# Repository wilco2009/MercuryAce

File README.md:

# Mercury Ace - a Jupiter Ace clone

[English version](README.md)

[Versión en Español](LEEME.md)

An open hardware and open source project (this is a readonly copy of this git https://codeberg.org/wilco2009/Mercury_Ace)

With permision of Paul Andrews, current owner of the brand.

## FEATURES

- 3KB/19KB bytes of RAM selectable by a jumper
- Normal (black background) or inverse video (white background) selectable by a jumper
- composite video output
- Reset button
- 4+4 selectable ROMs
- Ace81 add-on (Beta)

## THE CIRCUIT

### THE MEMORY MAP

### WORK RAM

The work memory is where all program data is stored.

In a standard Jupiter Ace, we have only 1KB of working memory, although there are standard 16KB expansion modules that allow us to have 17KB of working memory.

The Mercury Ace has a jumper (J3) that allows us to select between 3KB of RAM and 19KB (1KB and 17KB of working memory, respectively):

- 3KB (1KB Work RAM + 1KB Char RAM + 1KB BG RAM)
- 19KB (17KB Work RAM + 1KB Char RAM + 1KB BG RAM)

The Z29 chip is responsible for generating the enable signal for the working RAM, which is located starting at address 0x3C00. There are three copies of the first K of this memory starting from 0x3000.

Z29 decodes A12-A14, and since it only activates when A15 = 0 (G2B), it is only active in the first 32K, providing an output for each region within these ranges:

- Y0: 0K-4K
- Y1: 4K-8K
- Y2: 8K-12K
- Y3: 12K-16K
- Y4: 16K-20K
- Y5: 20K-24K
- Y6: 24K-28K
- Y7: 28K-32K

The Z30C and Z30D gates are used to replicate the mirrors of the first KB of the working memory from the original circuit in the 12K-16K memory area.

A14 indicates if we are in the 8-16K area. When A14 = 0, they need to be repeated, so they are fixed to always access the same RAM.

- 3KB		/CE=!(!A14*A13*A12)

- 19KB	/CE=!((!A14*A13*A12) + A14)

### BG RAM

The screen memory or BGRAM resides in the Z5-6 chip. As we can see in the memory map, it occupies the address ranges 0x2400..0x27ff and 0x2000..0x23ff (mirror).

The logical equations that govern the chip are as follows:

Z29.Y2 = not (not A15 and not A14 and A13 and not A12)

R26.OUT = Z16.2Y2 + Z29.Y2

/WE1 = Z26.11

READING

 | A11  | R26.out | /WE1 | CE(CHR) | CE2(BG)  | OE |
 | -----| --------| -----| --------| ---------| ---|
 |  0   |   0     |  1   |    1    |   0      |  0 |
 |  0   |   1     |  1   |    0    |   0      |  0 |
 |  1   |   0     |  1   |    0    |   1      |  0 |
 |  1   |   1     |  1   |    0    |   0      |  0 |

WRITTING

 | A11  | R26.out | /WE1 | CE(CHR) | CE2(BG)  | OE |
 | -----| --------|------| --------| ---------| ---|
 |  0   |   0     |  0   |    1    |   0      |  1 |
 |  0   |   1     |  1   |    0    |   0      |  0 |
 |  1   |   0     |  0   |    0    |   1      |  1 |
 |  1   |   1     |  1   |    0    |   0      |  0 |

The screen memory is configured as a block of 32x24 characters, which represents 768 bytes, leaving 254 bytes unused at the end of this memory.

This block can be accessed for both reading and writing.

The address bus of this chip is accessed from the CPU through the Z15 and Z16 chips and from the video circuit through resistors R11 to R20.

Access from the CPU or the video circuit is managed by the /VHOLD signal.

In the table above, we can see the logic for chip activation.

The case A11:R26.out:/WE1 = 1:1:1 appears to incorrectly address the BGRAM and CHARRAM when the processor is accessing memory outside the video area, but thanks to the resistors located between the data bus and the BGRAM, priority is given to the WORKRAM and ROM.

### CHAR RAM

/WE1 = Z26.11

The character memory, or CHAR RAM, occupies the address ranges 0x2c00..0x2fff and 0x2800..0x2BFF (mirror), containing a set of 128 characters, which represents 128x8=1024 bytes.

The memory can be addressed both from the CPU and the video circuit, but the CPU can only access it in write mode.

The reason for this is that during reading, the address bus entering from Z17 and Z18 is connected to the data bus through a 1KB resistor array, and the output generated by the chip is also connected to the same data bus through another 1KB array. As a result, the addresses interfere with the output data, generating incorrect readings. 

One possible solution could be to make the resistance value of the first array (address) higher than that of the second array (data), giving priority to the latter. However, this would need to be tested to rule out any unforeseen consequences.

When the video circuit is accessing the CHARRAM, the address bus arrives via two paths:

- A4..A9 come from the data output of the BGRAM (D0..D6), which at that moment will contain the character being displayed.

- A0..A3 correspond to the scanline of the character currently being displayed and will come from the lower part of the line counter (CNT9..CNT11).

Additionally, bit 7 of the character code data coming from the BGRAM will be stored in latch Z27B. This bit will be used to invert the video in Z23D if the bit is 1.

Bits 0 to 6 of the character code from the BGRAM are loaded into the serializer (Z28) each time the three lower bits of the horizontal counter are at zero (CNT0..CNT2), and the pixels are output from the chip with each clock pulse, combining with bit 7 (inverse) at the Z23D gate.

### VIDEO RAM ACCESS PRIORITY

The circuit implements a priority system that allows priority access to the video RAM (BGRAM + CHARRAM) to the CPU or the video circuit.

The video memory is duplicated in the form of a mirror in two memory zones depending on the value of A10.

The priority of access to the VRAM is different depending on whether we access the main block (A10=1) or its copy (A10=0).

When we access the video memory from the CPU (A14:A13:A12 = 0:1:0) (output of R26) and /VHOLD=1 Z15 and Z16 allow the address to pass from the bus.

If the access occurs with /VHOLD=0, the circuit sets the 2Y2 output of Z16 to 1, isolating the signals from the address bus and allowing access from the video circuit.

Once set to 1, the signal is memorized and remains in that state until /VHOLD is 1 again, at which point it will again allow access from the CPU.

Z29.Y2 = (A14:A13:A12 = 0:1:0)

 | /VHOLD  |   Z29.Y2   | Z16.2Y2 |   1G   | next 2Y2  | ADDR_OUT  |
 | --------| -----------| --------| -------| ----------| ----------|
 |    1    |      0     |    -    |    0   |     x     |    ADDR   |
 |    1    |      1     |    -    |    1   |     x     |     x     |
 |    0    |      0     |    0    |    0   |     0     |    ADDR   |
 |    0    |      1     |    0    |    1   |     1     |     x     |
 |    0    |      -     |    1    |    1   |     1     |     x     |

For /VHOLD to be equal to 0 A10 must be equal to 1, which corresponds to the upper copy of the video RAM. /VHOLD also activates a mechanism by which it implements a wait state in the CPU through the Z80 /WAIT signal to avoid interference with the video circuit.

However, if A10=0 (lower copy) we will not activate the /VHOLD signal and therefore we will be able to consult the RAM thanks to the fact that resistors R11 to R20 will give priority to the CPU, so in this case we will interfere with the display and may show garbage on the screen during access.

/WAIT = /VHOLD + Z29.Y2

/VHOLD = !VIDEN + !A10 (/VHOLD active (=0) when VIDEN=0 and A10=0)

### VIDEO CIRCUIT

The video generation circuit is based on two 9-bit counters generated with the Z9, Z10 and Z11 chips:

The horizontal pixel counter corresponds to the CNT0..CNT8 signals.

The line counter corresponds to the CNT9..CNT17 signals.

From the counters the circuit generates two main signals; LINE and FIELD.

The LINE signal (Z22.12) is activated to indicate the end of each line when the horizontal counter is between 320 and 351:

LINE= !CNT5*!CNT7*CNT6*CNT8

The FIELD signal is activated to indicate the end of the display of a frame when the line counter is between 248 and 255:

    FIELD=CNT12*CNT13*CNT14*CNT15*CNT16

Additionally, the VIDEN signal indicates when the rectangle containing the characters is being represented, delimited between 0 and 255 for the horizontal counter and between 0 and 191 for the line counter.
 
    VIDEN = !(CNT16*CNT15)*!(CNT17+CNT8)
 
 |CNT17    | CNT16   | CNT15  | Line      | Comment           |
 | --------| --------| -------| ----------|-------------------|
 |   0     |   0     |   0    |  0-63     | Part of VIDEN     |
 |   0     |   0     |   1    |  64-127   | Part of VIDEN     |
 |   0     |   1     |   0    |  128-191  | Part of VIDEN     |
 |   0     |   1     |   1    |  192-255  | Not Part of VIDEN |
 |   1     |   x     |   x    |  256-311  | Not part of VIDEN |
 
 | CNT8 | Pixel  | Comment           |
 | -----| -------| ------------------|
 | 0    | 0-255  | Part of VIDEN     |
 | 1    |256-415 | Not part of VIDEN |

The display sequence starts with the pixel counter and the line counter being set to zero, a combination of bits from the line counter and the pixel counter determines the position of the first character to be displayed in the BGRAM.

1) To do this, the BGRAM is addressed with bits CNT3,4,5,6,7,12,13,14,15,16, which gives us the character code through pins D0..D7 of the chip.

2) The character code returned by the chip together with the three lower bits of the line counter (CNT9..11) are used to address chip Z7-8 and obtain the scanline with the definition of the character which is loaded into the serializer Z28.

3) Bit 7 of the character code (inverse bit) is stored in Z27B to be combined with the scanline bits through Z23D.

4) From that moment on, at each clock cycle, a bit of the serializer content is output through pin 13 of the same and is inverted or not in Z23D depending on the content of Z27B and sent to the display.

5) When the value of CNT0..2 is 0 again, a new character code is loaded and the first scanline of said character is started. This process is repeated, sending 32 characters to the monitor.

6) After this, the pixels corresponding to the right edge are sent.

7) From 320 to 351 (LINE) a SYNC signal (positive pulse) is generated.

8) Between 352 and 385 we generate the Backporch signal.

9) Between 386 and 415 the right edge is painted.

10) The counter is reset to 0.

11) The above sequence (2-10) is repeated for the next scanline up to a total of 8 (CNT9..11=111b) at which point we move on to addressing the next line in the BGRAM.

12) After displaying 24 lines (line counter=192) we move to the lower edge of the screen, generating the FIELD signal between the value 248 and 255 which causes a new SYNC signal. Additionally, an interrupt is generated in the Z80 /INT=0.

13) Finally, the upper edge of the screen is generated between 256 and 311.

14) When the line counter reaches the value 312 it is reset to 0 again and we begin displaying a new frame.

BACKPORCH = !CNT5*CNT2 from the last SYNC

### ACE81 ADDON (only valid until build025)

What is the ACE81 ADDON?
The ACE81 is a small module that plugs over the BGRAM and slightly modifies the display control hardware so that it is capable of managing a display like that of a ZX81.
The ZX81 makes extensive use of the processor to generate video, to the point that about two thirds of the processor's time is spent on this purpose.
The JA is a machine very similar to the ZX81 in many aspects, but with video generation hardware, which makes the 3.2MHz at which it operates fully available for our program.
The idea (and design) of the ACE81 came from Pedro Gimeno as an exercise in what a ZX81 would have been like if, like the JA, it had had dedicated hardware to generate video.
Obviously it would have been a much faster machine (or slower, depending on how we want to approach it).
The idea is to run a ZX81 ROM on a JA, with minimal modifications to the ROM to eliminate the video generation part.
Comparing the video memory of the ZX81 and the JA we realize that their layout is practically the same:

Similarities
- Both have 32x24 characters
- Both are black and white
- In both cases bit 7 of the character code is "inverse video"

Differences
- The character set of the JA is 128 elements, while in the ZX81 it is only 64 because bit 6=1 is used by the firmware to detect the end of line.
- In ZX81 each line is terminated in a HALT (cod=76h) (33x24=792 bytes) while in JA there is no line terminator (768 bytes)

Based on these premises the idea of ​​Ace81 is to make the video memory structure the same as that of the zx81 when we have activated the ZX81 mode (33 bytes per line), maintaining the standard structure (32 bytes per line) when the JA mode is selected.

Apart from the differences in the display, there is a small difference in the keyboard layout that requires modifying the circuitry of this to maintain the physical order of the keys.

Physically the layout of the keys of the ZX81 is identical to that of the JA, however unlike the JA, in the ZX81 the physical layout coincides with the logical one, which makes compatibility difficult when using a JA keyboard with the ZX81 ROM.
To overcome this problem, the keyboard wiring must be modified and some additional logic must be added, which we have decided to include in a GAL to facilitate the design.

As I mentioned before, the changes are limited to the two lower half-rows (half-row 0 and half-row 7).

| half-row| ZX81		      | Jupiter Ace	    |
|---------|-------------------|-----------------|
|    0    | SHIFT   Z   X C V | SHIFT SYMB Z X C|
|    7    | SPACE SYMB	N M B | SPACE  N   M B V|

But that small change and making both modes selectable, implies important modifications in the keyboard connection logic, since it completely changes the structure of the half-rows 0 and 7.

The equations that control both modes are the following:

```
/** Logic Equations **/

   ZX81 = ACE81_ENABLED;
   Jupiter = !ACE81_ENABLED;
   
   ROW_SS = !((Jupiter & !ROW1) # (ZX81 & !ROW8)); 
   ROW_V = !((Jupiter & !ROW8) # (ZX81 & !ROW1)); 
   
   KEYB2 = !(Jupiter & !KM & !ROW8 # ZX81 & !KZ & !ROW1 );
   KEYB3 = !(Jupiter & (!KN & !ROW8 # !KZ & !ROW1) # ZX81 & (!KM & !ROW8 # !KX & !ROW1)); 
   KEYB4 = !(Jupiter & (!KB & !ROW8 # !KX & !ROW1) # ZX81 & (!KN & !ROW8 # !KC &!ROW1));
   KEYB5 = !(Jupiter & !KC & !ROW1 # ZX81 & !KB & !ROW8);
```

### Hires plus 512KB memory ADDON (valid from Build026)

- Ace81 addon included 
- ROM page selected by software 
- High resolution 256x192 pixels 
- 32 pages in text-mode and 5 pages in high-resolution mode.
- 32 character sets in memory simultaneously.
- Shadow screen (CPU can access any of the video pages regardless of which one is currently being viewed).
- Extra 512KB of User RAM plus the internal 16KB

All the functionality of the Addon is managed via port E3, through a command system. 

Each command has its read equivalent, allowing us to check the status at any time. Below is a table with the available commands:

**Write mode**		

```
	ld a,cccddddd
	OUT ($e3),a
```
```  
	where 
        ccc = command;
        ddddd = param
```

| command |param         |description                             |
|---------|--------------|----------------------------------------|
| 000b	  |5 bit PAGE    |BG-RAM access page from CPU             |
| 001b	  |5 bit PAGE    |BG-RAM access page from video hardware  |
| 010b    |5 bit PAGE    |CHR-RAM access page from CPU            |
| 011b	  |5 bit PAGE    |CHR-RAM access page from video hardware |
| 100b	  |video mode    |00000b = Text mode, 00001b = Hires mode |
| 101b	  |4 bit PAGE    |USER RAM PAGE                           |
| 110b	  |0mppp         |(m=1 disable ace81)  ppp=ROM PAGE       |
| 111b	  |5bits subline |offset of hires page in lines           |
		
**Read mode**		

```
	ld a,ccc-----		
	in a,($e3)		
```
```  
	where 
        ccc = command;  returns result in register A"		
```

| command |result        |description                             |
|---------|--------------|----------------------------------------|
| 000b    |5 bit PAGE    |BG-RAM access page from CPU             |
| 001b	  |5 bit PAGE    |BG-RAM access page from video hardware  |
| 010b	  |5 bit PAGE    |CHR-RAM access page from CPU            |
| 011b	  |5 bit PAGE    |CHR-RAM access page from video hardware |
| 100b	  |video mode    |00000b = Text mode, 00001b = Hires mode |
| 101b	  |4 bit PAGE    |USER RAM PAGE                           |
| 110b	  |0mppp         |(m=1 disable ace81)  ppp=ROM PAGE       |
| 111b	  |5bits subline |offset of hires page in lines           |

### Operation of Video RAM and Character RAM Paging

The video and character RAM pages displayed are independently selectable from the video and character RAM pages accessed by the CPU.

For example, if we switch to page 1 with command 0, all CPU accesses will be redirected to page 1 of the BGRAM, but the video hardware will continue displaying page 0. The same applies to CHRRAM.

This configuration allows us to write in the background to a page that isn’t being displayed and then visualize it instantly by switching the active page for the hardware with command 1, avoiding glitches.

### Operation of Hires Mode

The Hires mode works by using 6 pages of text simultaneously (or 7, as we will see later), the BGRAM page selected for the hardware (henceforth referred to as VIDEO-BGPAGE) and the 5 subsequent pages.
The addressing space will continue to be 1024 bytes (2400h..27FFh), so it will be the programmer's responsibility to switch pages to access the 6KB of video memory.
Since each page has a size of 1KB, it will contain 32 lines (32*32=1024 bytes).

If we use only command 1, the hardware will start reading pixel line 0 from position 0 of the VIDEO-BGPAGE. However, using the page offset command (111b), we can specify a starting position offset (sub-line) within the VIDEO-BGPAGE.
This offset will affect only the display, while CPU access remains unaffected.
For example, if VIDEO-BGPAGE=0 and sub-line=10, the hardware will display the memory content starting at page 0, memory position 320 (32 bytes * 10 lines), and ending at page 7, position 319.

This command can be very useful for performing vertical scrolling via hardware.

Below, we can see a map of the video screen in high-resolution mode.

In this mode, the hardware displays characters with only one pixel of height, so the character definitions must match the binary representation of the code. The hires mode operation requires a prior configuration of character RAM. Before switching to hires mode, we must configure the character set as follows:

The first 4 scanlines of the active 128-character set must contain 4 copies of the character code in binary, and the last four scanlines should contain the character code XOR 127.

scanline/Addr |    0    |    8    |    16   |.........|  1016   |
--------------|---------|---------|---------|---------|---------|
 Addr+0       |00000000 |00000001 |00000010 |-------- |01111111 |
 Addr+1       |00000000 |00000001 |00000010 |-------- |01111111 |
 Addr+2       |00000000 |00000001 |00000010 |-------- |01111111 |
 Addr+3       |00000000 |00000001 |00000010 |-------- |01111111 |
 Addr+4       |01111111 |01111110 |01111101 |-------- |00000000 |
 Addr+5       |01111111 |01111110 |01111101 |-------- |00000000 |
 Addr+6       |01111111 |01111110 |01111101 |-------- |00000000 |
 Addr+7       |01111111 |01111110 |01111101 |-------- |00000000 |
 
### USER RAM PAGING

The 512KB of extra RAM for the user is set up in 32KB pages that occupy the second half of the Z80's addressing space.

The active page is selected using command 101b followed by the page number. Since we have 512KB of RAM, we have a total of 16 32KB pages.

### SWITCHING THE ACTIVE ROM BY SOFTWARE
Immediately after a reset, or when powering up the system, the active ROM will be the one selected by the ROM selection DIP switches. The ROM can be changed by software using command 110b followed by the ROM page. We have a total of 8 8KB ROM pages, so we need 3 bits for selection (bits 0 to 2 of register A).

### ACE81 MODE

Under normal conditions, ROMs 6 and 7 are reserved for ACE81 mode. This differs from the ACE81 addon, where ROMs 4, 5, 6, and 7 were reserved for this mode.

In addition to the previous change, the Hires Add-on includes an option to disable this mode so that ROMs 6 and 7 become normal ROMs. To disable ACE81 mode, use the ROM selection command. Setting bit 3 of register A to 1 during the ROM selection command call will disable ACE81 mode until the next reset or until the command is used again with bit 3 set to 0.

## ASSEMBLY

The Mercury Ace project is sponsored by [PCBWay](https://www.pcbway.com/)​. The high quality of their boards, the speed of manufacturing and shipping, and their high-tech process have greatly helped us achieve our goals.

Components that should be changed or should not be put in or changed during the assembly

- C4 – Do not place
- U2,R4,R32,R33,R34 – Do not place if SJ1 closes (video option)
- JP9 – Do not place if the Ace81 board is not in place
- SJ2-SJ9 – place if the Ace81 board is not in place
- R30 & R31 – Do not place if the Ace81 board is not in place
- D12.. D17 – install a 0R instead the diodes if the Ace81 board is not on
- JP17 - place always
- JP11 - place always 1-2,3-4,5-6,7-8,9-10
- JP12 - place always 1-2,3-4,5-6,7-8,9-10

We have the following options when building the board:

Installation of op-amp for video:

The SJ1 bridge is the one that will allow us to select whether to install the op-amp circuit or bypass it.

With the bridge open, the video will pass through the components of the op-amp and therefore we will need to install the following components:

-	U2
-	R4
-	R32
-	R33
-	R34

If you decide not to use the op-amp, you must close SJ1 with a drop of tin and not solder the aforementioned components.

Installing the Ace81 add-on module:

The Ace81 Add-On module is a circuit that is currently in Beta. This circuit modifies the Jupiter Ace's hardware to simulate a zx81, modifying the video generation circuit and keyboard order.

In the module we have a selector that will allow us to switch between Jupiter Ace mode and Ace81 mode.

If we want to have this add-on we must take in acount the follwing:

Do not install the following components: R30, R31, D12, D13, D14, D15, D16, D17, and Z40.
Bridge D12, D13, D14, D15, D16, and D17.

The JED file for the GAL(Z40) is available in the GAL folder.

Additionally, the Add-on board will have to be manufactured and connected on the pins located around the Z5-6 RAM (JP10x, JP15x, JP6 and JP8)

JP9 is an alternate selector on the main board for ACE81 mode, so JP9 and the Addon selector are mutually exclusive, so only one of them should be used, leaving the other one unset.

This mode requires a modified ROM for its proper functioning that is included inside the ROM folder.

The GAL must be welded without a socket as it does not fit inside the housing along with it.

If you do not use the Ace81 mode, you must take into account the following:

Install the following components: R30, R31, D12, D13, D14, D15, D16, D17, and Z40.

Close the JP10x, JP15x, JP6 and JP8 jumpers.

Close the SJ2 jumpers with a drop of tin. SJ9

## ROM

The clone allows to have 4 ROMs in Jupiter Ace mode and 4 ROMs in Ace81 mode, selectable from DIPSwitch S1. Pin 1 of S1 selects the mode (ON=ACE81 MODE, OFF=Jupiter ACE MODE).

The addon's mode selector will automatically switch between one block of 4 ROMs or the other, while S1 will allow you to manually select any of the 4 ROMs.

In the ROM folder we can find the following files:
- "ace.rom" - Original Jupiter Ace ROM
- "ace81.rom" - ZX81 ROM modified by Pedro Gimeno to work with the clone together with the Ace81 Add-on
- testrom.rom - diagnostics ROM made by Pedro Gimeno (https://codeberg.org/pgimeno/jupace-testrom)
- MercuryAce.bin - Contains all previous files in one unique file ready to be burned in an EEPROM.

| FILE      | MODE        | Z1.2 ADDR    | S1.1 | S1.2 | S1.3 |
| -----     | ------------| -------------| -----| -----| -----|
| ace.rom   | Jupiter Ace | 0000h..1fffh |  ON  |  ON  |  ON  |
| test.rom  | Jupiter Ace | 2000h..3fffh |  ON  |  ON  | OFF  |
| ace.rom   | Jupiter Ace | 4000h..5fffh |  ON  | OFF  |  ON  |
| test.rom  | Jupiter Ace | 6000h..7fffh |  ON  | OFF  | OFF  |
| ace81.rom | ZX81        | 8000h..9fffh | OFF  |  ON  |  ON  |
| test.rom  | ZX81        | a000h..bfffh | OFF  |  ON  | OFF  |
| ace81.rom | ZX81        | c000h..dfffh | OFF  | OFF  |  ON  |
| test.rom  | ZX81        | e000h..ffffh | OFF  | OFF  | OFF  |

## PARTLIST

### CLONE

 |Part	                               |Value   |Device     |Package    |Description	  |NO ACE81	     |ACE81	 |SJ1 CLOSED |SJ1 OPENED |
 | ------------------------------------| -------| ----------| ----------| ----------------| -------------| ------| ----------| ----------| 
 |K1..K41		                       |        |PUSH BUTTON|B3F-40     |OMRON	          |     Y        |  Y    |   Y       |   Y       |
 |R35                                  | 300R   |RESISTOR   |0204/7     |                 |	    Y		 |  Y    |   Y       |   Y       |
 |R26	                               | 330R   |RESISTOR   |0204/7     |                 |	    Y		 |  Y    |   Y       |   Y       |			
 |R28,R29                              | 680R   |RESISTOR   |0204/7     |                 |	    Y		 |  Y    |   Y       |   Y       |			
 |R32                                  | 200    |RESISTOR   |0204/7     |                 |	     		 |       |   N       |   Y       |			
 |R33                                  | 200    |RESISTOR   |0204/7     |                 |	     		 |       |   N       |   Y       |			
 |R34                                  | 75    |RESISTOR   |0204/7     |                 |	     		 |       |   N       |   Y       |			
 |R8,R10,R24,R25,R27,R39,R43           | 10K    |RESISTOR   |0204/7     |                 |	    Y		 |  Y    |   Y       |   Y       |			
 |R5                                   | 12K    |RESISTOR   |0204/7     |                 |	    Y		 |  Y    |   Y       |   Y       |			
 |R3                                   | 500R   |POT        |EU-B25P    | POTENTIOMETER   |	    Y		 |  Y    |   Y       |   Y       |			
 |R4                                   | 1K     |POT        |EU-B25P    | POTENTIOMETER   |	    Y		 |  Y    |   Y       |   Y       |			
 |R44                                  | 1K     |POT        |EU-B25P    | POTENTIOMETER   |	    Y		 |  Y    |   Y       |   Y       |			
 |R1,R6,R11..R23,R100..R107,R200..R207 | 1K     |RESISTOR   |0204/7     |                 |	     		 |       |   N       |   Y       |			
 |R42                                  | 1K     |RESISTOR   |0204/7     |                 |	     		 |       |   N       |   Y       |			
 |R45,R46,R47                          | 470R   |RESISTOR   |0204/7     |                 |	     		 |       |   N       |   Y       |			
 |R9                                   | 22K    |RESISTOR   |0204/7     |                 |	    Y		 |  Y    |   Y       |   Y       |			
 |R7                                   | 33K    |RESISTOR   |0204/7     |                 |	    Y		 |  Y    |   Y       |   Y       |			
 |R2                                   | 47K    |RESISTOR   |0204/7     |                 |	    Y		 |  Y    |   Y       |   Y       |			
 |R30,R31                              | 4K7    |RESISTOR   |0204/7     |                 |	    N		 |  Y    |   Y       |   Y       |			
 |R36..R38,R40,R41                     | 4K7    |RESISTOR   |0204/7     |                 |	    Y		 |  Y    |   Y       |   Y       |			
 |R45..R47                             | 470R   |RESISTOR   |0204/7     |                 |	    Y		 |  Y    |   Y       |   Y       |			
 |RN1 (alt to R36,R37,R38,R40,R41)     | 4K7    |RNET       |RN-6       | RESISTOR NET    |	    Y		 |  Y    |   Y       |   Y       |			
 |C4 (DO NOT INSTALL)                  |        |CAPACITOR  |025X50     | CERAMIC  CAP.   |	    N		 |  N    |   N       |   N       |			
 |C10,C13..C21                         | 100nF  |CAPACITOR  |025X50     | CERAMIC  CAP.   |	    Y		 |  Y    |   Y       |   Y       |			
 |C2                                   | 100pF  |CAPACITOR  |025X50     | CERAMIC  CAP.   |	    Y		 |  Y    |   Y       |   Y       |			
 |C9                                   | 100uF  |CAPACITOR  |RADIAL     | POL. CAPACITOR  |	    Y		 |  Y    |   Y       |   Y       |			
 |C7,C11,C12                           | 1uF    |CAPACITOR  |RADIAL     | POL. CAPACITOR  |	    Y		 |  Y    |   Y       |   Y       |			
 |C8                                   | 2.2nF  |CAPACITOR  |025X50     | CERAMIC  CAP.   |	    Y		 |  Y    |   Y       |   Y       |			
 |C3                                   | 2.2uF  |CAPACITOR  |025X50     | CERAMIC  CAP.   |	    Y		 |  Y    |   Y       |   Y       |			
 |C1                                   | 30pF   |CAPACITOR  |025X50     | CERAMIC  CAP.   |	    Y		 |  Y    |   Y       |   Y       |			
 |C22                                  | 470pF  |CAPACITOR  |025X50     | CERAMIC  CAP.   |	    Y		 |  Y    |   Y       |   Y       |			
 |C6                                   | 47nF   |CAPACITOR  |025X50     | CERAMIC  CAP.   |	    Y		 |  Y    |   Y       |   Y       |			
 |C5                                   | 47pF   |CAPACITOR  |025X50     | CERAMIC  CAP.   |	    Y		 |  Y    |   Y       |   Y       |			
 |C23                                  | 10pF   |CAPACITOR  |025X50     | CERAMIC  CAP.   |	    Y		 |  Y    |   Y       |   Y       |			
 |D1..D11                              | 1N4148 |DIODE      |DO35-7     | SIGNAL DIODE    |	    Y		 |  Y    |   Y       |   Y       |			
 |D12..D17                             | 1N4148 |DIODE      |DO35-7     | SIGNAL DIODE    | REP.WITH 0R  |  Y    |           |           |			
 |U1                                   | 7805   |REGULATOR  |TO220      | 5V REGULATOR    |      Y       |  Y    |   Y       |   Y       |			
 |Q1                                   | 2N3904 |TRANSISTOR |TO92       | NPN             |      Y       |  Y    |   Y       |   Y       |			
 |X1                                   | 6.5MHZ |CRISTAL    |HC49U      |                 |      Y       |  Y    |   Y       |   Y       |			
 |Z0                                   | Z80A   |CPU        |DIL40      |                 |      Y       |  Y    |   Y       |   Y       |			
 |Z1-2                                 | 27C512 |EEPROM     |DIL28W     | 64KB x 8 BITS   |      Y       |  Y    |   Y       |   Y       |			
 |Z1,Z27                               | 74LS74 |74XX       |DIL14      | DUAL D-FLIP FLOP|      Y       |  Y    |   Y       |   Y       |			
 |Z3-4,Z5-6,Z7-8                       | 62256  |SRAM       |DIL28W     | 32KB x 8 BITS   |      Y       |  Y    |   Y       |   Y       |			
 |Z9,Z10,Z11                           | 74LS393|74XX       |DIL14      | DUAL BIN.COUNTER|      Y       |  Y    |   Y       |   Y       |			
 |Z14..Z18                             | 74LS367|74XX       |DIL16      | 3-STATE BUFFER  |      Y       |  Y    |   Y       |   Y       |			
 |Z19,Z30,Z41                          | 74LS00 |74XX       |DIL14      | 4xNAND GATES    |      Y       |  Y    |   Y       |   Y       |			
 |Z20                                  | 74LS08 |74XX       |DIL14      | 4xAND GATES     |      Y       |  Y    |   Y       |   Y       |			
 |Z21,Z22,Z31                          | 74LS11 |74XX       |DIL14      | 3xAND GATES     |      Y       |  Y    |   Y       |   Y       |			
 |Z23                                  | 74LS86 |74XX       |DIL14      | 4xXOR GATES     |      Y       |  Y    |   Y       |   Y       |			
 |Z24,Z25                              | 74LS02 |74XX       |DIL14      | 4xNOR GATES     |      Y       |  Y    |   Y       |   Y       |			
 |Z26                                  | 74LS32 |74XX       |DIL14      | 4xOR GATES      |      Y       |  Y    |   Y       |   Y       |			
 |Z29                                  | 74LS138|74XX       |DIL16      | DECODER         |      Y       |  Y    |   Y       |   Y       |			
 |Z28                                  | 74LS166|74XX       |DIL16      | 8BIT SHIFT REG. |      Y       |  Y    |   Y       |   Y       |			
 |Z40                                  | GAL16V8|GAL        |DIL20      | GAL16V8         |      N       |  Y    |           |           |			
 |LED1                                 | RED    |LED        |3MM        | POWER LED       |      Y       |  Y    |   Y       |   Y       |			
 |LED2                                 | YELLOW |LED        |3MM        | ACE81 LED       |      N       |  Y    |           |           |			
 |Q3                                   | BC337  |TRANSISTOR |TO92       | NPN             |      Y       |  Y    |   Y       |   Y       |			
 |X2                                   | YELLOW |CONNECTOR  |AV-8.4-5   | 3 PINS          |      Y       |  Y    |   Y       |   Y       |			
 |LS1                                  | 16R    |BUZZER     |           | PASIVE BUZZER   |      Y       |  Y    |   Y       |   Y       |			
 |U2                                   | MAX4390|           |SOT95P280  | op-amp          |              |       |   Y       |   N       |			
 |EAR,MIC,POWER	JACK                   | 3.5mm  |CONNECTOR  |PJ302M     | FEM. 3.5mm JACK |      Y       |  Y    |   Y       |   Y       |			
 |S2				                   |        |BUTTON     |B3F-31XX   | PUSH BUTTON 90º |      Y       |  Y    |   Y       |   Y       |			
 |S1				                   | DS02   |DIPSWITCH  |DS-03      | ROM SELECTOR    |      Y       |  Y    |   Y       |   Y       |			
 |JP4				                   | SPDT   |SELECTOR   |pitch 2.54 | BACKGROUND SEL. |      Y       |  Y    |   Y       |   Y       |			

### ACE81

 |Part	                               |Value   |Device     |Package    |Description	  |
 | ------------------------------------| -------| ----------| ----------| ----------------| 
 |IC1,IC2,IC5	                       | 74LS283|74XX       |SOP16      |4bit bin. adder  |
 |IC3,IC4		                       | 74LS08 |74XX       |SOP14      |4xAND gates      |

### HIRES
 |Part	                               |Value     |Device     |Package    |Description	    |
 | ------------------------------------| ---------| ----------| ----------| ----------------| 
 |U1        	                       | XC95144XL|CPLD       |TQG100     |XILINX CPLD      |
 |IC1        	                       | 74LS00   |74XX       |SOP14      |XILINX CPLD      |
 |R1..R8                               | 10K      |RESISTOR   |0204/7     |RESISTOR         |
 |R9                                   | 680R     |RESISTOR   |0204/7     |RESISTOR         |
 |LED1                                 | YELLOW   |LED        |3MM        | ACE81 LED       | 

## THE CASE

The clone case is based on an initial design by Cees Meijer, modified by him under my guidance later on, and some final modifications by myself to adapt it to my clone.

Many thanks to Cees for his design.

The Mercury Ace PCB is designed to be able to replace the PCB of the original Jupiter Ace, fitting perfectly into its case.

In the same way, I have modified the Cees Meijer model to be as similar as possible to the original case and also be able to house both the clone PCB and an original Jupiter Ace PCB.

The ready-to-print STL files are available in the STL folder. The case in the cover photo is printed in 9000x resin and I am very happy with the result.

The case consists of two pieces that must be printed in white.

For the bottom part we have two alternatives:

- The file "Jupiter ACE (bottom).stl" does not allow access to the DIP Switch of the selector so the aesthetics will be more similar to the original. We can leave the DIPSwitch uninstalled and the clone will boot by selecting the ROM recorded in the lowest part of the chip.
- The file "Jupiter ACE (bottom)(ROM selector).stl", leaves a window to access the ROM DIP Switch and the Ace81 selector.

For the keys we will need three printed copies of the file "keys (without space key).stl" and one copy of the file "keys (with space key).stl". This will give us the 40 keys we need.

The rivets needed are like the ones in the photo. We must look for them in online stores as nylon rivets reference R3100 to hold the PCB to the case and R3065 for those that join the two parts of the case.

The case stickers are available in the Adobe Illustrator file "teclado_cuadriculado v2 (1).ai".

We must print the file on transparent adhesive plastic and use a printer capable of printing with white ink. The blue background is for reference only and should not be printed.

## REFERENCES

https://en.wikipedia.org/wiki/Jupiter_Cantab

https://es.wikipedia.org/wiki/Jupiter_Ace

https://hackaday.io/project/165772-recreating-the-jupiter-ace

http://searle.x10host.com/JupiterAce/JupiterAce.html

https://codeberg.org/pgimeno/jupace-testrom

## ACKNOWLEDGEMENTS

Richard Altwasser and Steven Vickers for designing such a wonderful machine

Pedro Gimeno for his selfless help and for the design of the Ace81 and the modified ROM

Paul Andrews (current owner of the Jupiter Ace brand) for allowing the development of the clone

Cees Meijer for providing me with the initial design of the case

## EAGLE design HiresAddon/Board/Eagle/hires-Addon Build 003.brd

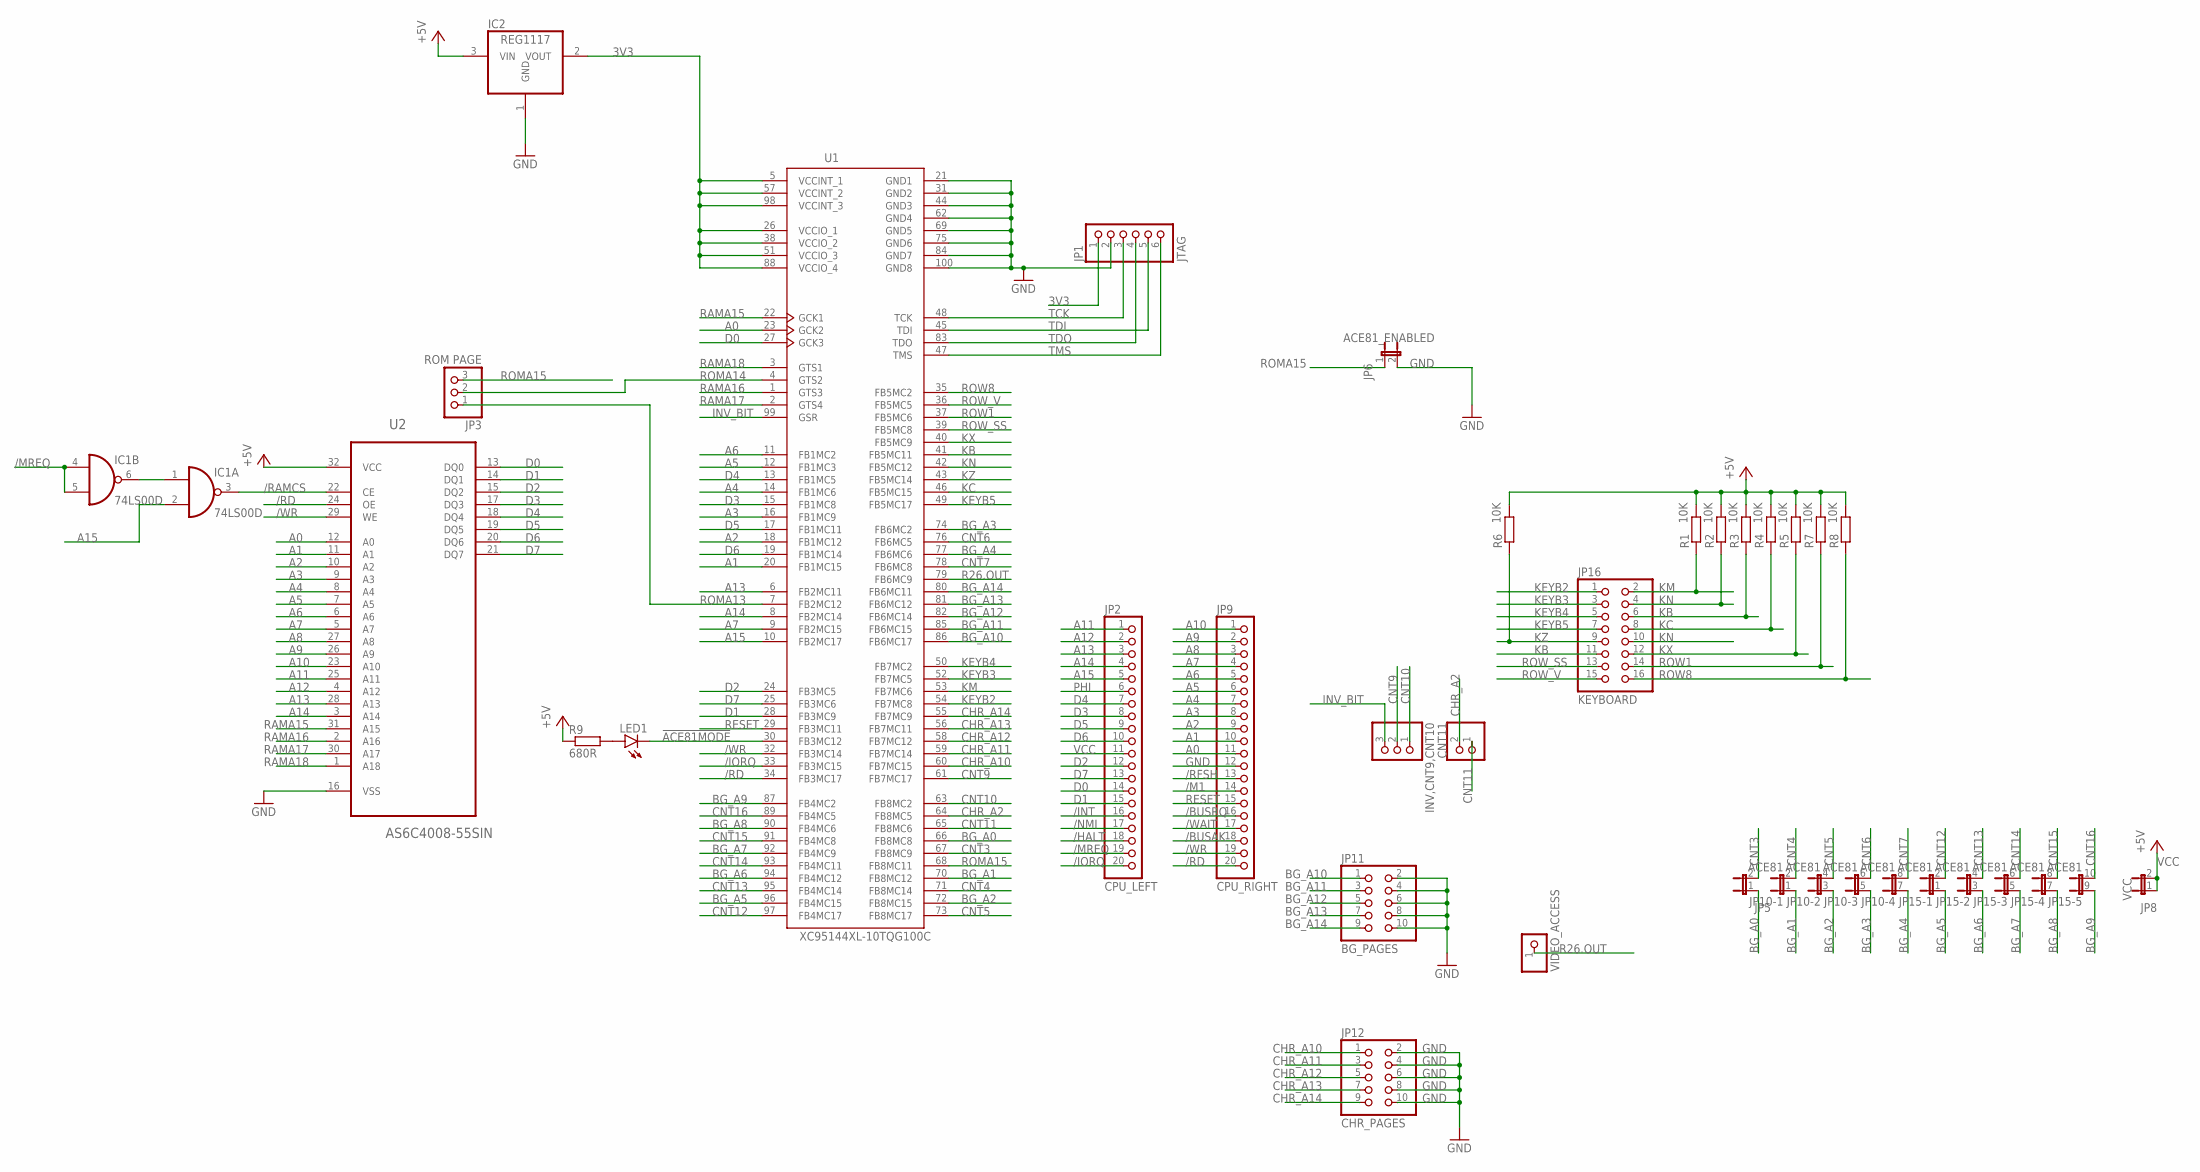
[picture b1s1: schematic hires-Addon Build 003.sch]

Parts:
CNT11: PINHD-1X2; 1X02
IC1: 74LS00D; SO14
IC2: REG1117; SOT223
INV,CNT9,CNT10: PINHD-1X3; 1X03
JP1: JTAG; 1X06/90
JP2: CPU_LEFT; 1X20
JP3: ROM PAGE; 1X03
JP5: JP1E1Q; JP1Q
JP6: ACE81_ENABLED; JP1Q
JP8: VCC; JP1Q
JP9: CPU_RIGHT; 1X20
JP10: ACE81; JP4Q
JP11: BG_PAGES; 2X05
JP12: CHR_PAGES; 2X05
JP14: VIDEO_ACCESS; 1X01
JP15: ACE81; JP5Q
JP16: KEYBOARD; 2X08
LED1: LED3MM
R1, R2, R3, R4, R5, R6, R7, R8: 10K; 0204/7
R9: 680R; 0204/7
U1: XC95144XL-10TQG100C; TQFP100
U2: AS6C4008-55SIN; SOIC127P1407X299-32N

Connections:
3V3: IC2.2 (VOUT), JP1.1, U1.5 (VCCINT_1), U1.26 (VCCIO_1), U1.38 (VCCIO_2), U1.51 (VCCIO_3), U1.57 (VCCINT_2), U1.88 (VCCIO_4), U1.98 (VCCINT_3)
!ACE81MODE: LED1.K (C), U1.30 (FB3MC12)
/BUSAK: JP9.18
/BUSRQ: JP9.16
/HALT: JP2.18
/INT: JP2.16
/IORQ: JP2.20, U1.33 (FB3MC15)
/M1: JP9.14
/MREQ: IC1.4 (I0), IC1.5 (I1), JP2.19
/NMI: JP2.17
/RAMCS: IC1.3 (O), U2.22 (CE)
/RD: JP9.20, U1.34 (FB3MC17), U2.24 (OE)
/RFSH: JP9.13
/WAIT: JP9.17
/WR: JP9.19, U1.32 (FB3MC14), U2.29 (WE)
A0: JP9.11, U1.23 (GCK2), U2.12 (A0)
A1: JP9.10, U1.20 (FB1MC15), U2.11 (A1)
A2: JP9.9, U1.18 (FB1MC12), U2.10 (A2)
A3: JP9.8, U1.16 (FB1MC9), U2.9 (A3)
A4: JP9.7, U1.14 (FB1MC6), U2.8 (A4)
A5: JP9.6, U1.12 (FB1MC3), U2.7 (A5)
A6: JP9.5, U1.11 (FB1MC2), U2.6 (A6)
A7: JP9.4, U1.9 (FB2MC15), U2.5 (A7)
A8: JP9.3, U2.27 (A8)
A9: JP9.2, U2.26 (A9)
A10: JP9.1, U2.23 (A10)
A11: JP2.1, U2.25 (A11)
A12: JP2.2, U2.4 (A12)
A13: JP2.3, U1.6 (FB2MC11), U2.28 (A13)
A14: JP2.4, U1.8 (FB2MC14), U2.3 (A14)
A15: IC1.2 (I1), JP2.5, U1.10 (FB2MC17)
BG_A0: JP5.1, U1.66 (FB8MC8)
BG_A1: JP10.1, U1.70 (FB8MC12)
BG_A2: JP10.3 (1), U1.72 (FB8MC15)
BG_A3: JP10.5 (1), U1.74 (FB6MC2)
BG_A4: JP10.7 (1), U1.77 (FB6MC6)
BG_A5: JP15.1, U1.96 (FB4MC15)
BG_A6: JP15.3 (1), U1.94 (FB4MC12)
BG_A7: JP15.5 (1), U1.92 (FB4MC9)
BG_A8: JP15.7 (1), U1.90 (FB4MC6)
BG_A9: JP15.9 (1), U1.87 (FB4MC2)
BG_A10: JP11.1, U1.86 (FB6MC17)
BG_A11: JP11.3, U1.85 (FB6MC15)
BG_A12: JP11.5, U1.82 (FB6MC14)
BG_A13: JP11.7, U1.81 (FB6MC12)
BG_A14: JP11.9, U1.80 (FB6MC11)
CHR_A2: CNT11.2, U1.64 (FB8MC5)
CHR_A10: JP12.1, U1.60 (FB7MC15)
CHR_A11: JP12.3, U1.59 (FB7MC14)
CHR_A12: JP12.5, U1.58 (FB7MC12)
CHR_A13: JP12.7, U1.56 (FB7MC11)
CHR_A14: JP12.9, U1.55 (FB7MC9)
CNT3: JP5.2, U1.67 (FB8MC9)
CNT4: JP10.2, U1.71 (FB8MC14)
CNT5: JP10.4 (2), U1.73 (FB8MC17)
CNT6: JP10.6 (2), U1.76 (FB6MC5)
CNT7: JP10.8 (2), U1.78 (FB6MC8)
CNT9: INV,CNT9,CNT10.2, U1.61 (FB7MC17)
CNT10: INV,CNT9,CNT10.1, U1.63 (FB8MC2)
CNT11: CNT11.1, U1.65 (FB8MC6)
CNT12: JP15.2, U1.97 (FB4MC17)
CNT13: JP15.4 (2), U1.95 (FB4MC14)
CNT14: JP15.6 (2), U1.93 (FB4MC11)
CNT15: JP15.8 (2), U1.91 (FB4MC8)
CNT16: JP15.10 (2), U1.89 (FB4MC5)
D0: JP2.14, U1.27 (GCK3), U2.13 (DQ0)
D1: JP2.15, U1.28 (FB3MC9), U2.14 (DQ1)
D2: JP2.12, U1.24 (FB3MC5), U2.15 (DQ2)
D3: JP2.8, U1.15 (FB1MC8), U2.17 (DQ3)
D4: JP2.7, U1.13 (FB1MC5), U2.18 (DQ4)
D5: JP2.9, U1.17 (FB1MC11), U2.19 (DQ5)
D6: JP2.10, U1.19 (FB1MC14), U2.20 (DQ6)
D7: JP2.13, U1.25 (FB3MC6), U2.21 (DQ7)
GND: IC1.7 (GND), IC2.1 (GND), JP1.2, JP6.2, JP9.12, JP11.2, JP11.4, JP11.6, JP11.8, JP11.10, JP12.2, JP12.4, JP12.6, JP12.8, JP12.10, U1.21 (GND1), U1.31 (GND2), U1.44 (GND3), U1.62 (GND4), U1.69 (GND5), U1.75 (GND6), U1.84 (GND7), U1.100 (GND8), U2.16 (VSS)
INV_BIT: INV,CNT9,CNT10.3, U1.99 (GSR)
KB: JP16.6, JP16.11, R3.1, U1.41 (FB5MC11)
KC: JP16.8, R4.1, U1.46 (FB5MC15)
KEYB2: JP16.1, U1.54 (FB7MC8)
KEYB3: JP16.3, U1.52 (FB7MC5)
KEYB4: JP16.5, U1.50 (FB7MC2)
KEYB5: JP16.7, U1.49 (FB5MC17)
KM: JP16.2, R1.1, U1.53 (FB7MC6)
KN: JP16.4, JP16.10, R2.1, U1.42 (FB5MC12)
KX: JP16.12, R5.1, U1.40 (FB5MC9)
KZ: JP16.9, R6.1, U1.43 (FB5MC14)
unnamed: IC1.1 (I0), IC1.6 (O)
unnamed: LED1.A, R9.2
PHI: JP2.6
R26.OUT: JP14.1, U1.79 (FB6MC9)
RAMA15: U1.22 (GCK1), U2.31 (A15)
RAMA16: U1.1 (GTS3), U2.2 (A16)
RAMA17: U1.2 (GTS4), U2.30 (A17)
RAMA18: U1.3 (GTS1), U2.1 (A18)
RESET: JP9.15, U1.29 (FB3MC11)
ROMA13: JP3.1, U1.7 (FB2MC12)
ROMA14: JP3.2, U1.4 (GTS2)
ROMA15: JP3.3, JP6.1, U1.68 (FB8MC11)
ROW1: JP16.14, R7.1, U1.37 (FB5MC6)
ROW8: JP16.16, R8.1, U1.35 (FB5MC2)
ROW_SS: JP16.13, U1.39 (FB5MC8)
ROW_V: JP16.15, U1.36 (FB5MC5)
TCK: JP1.3, U1.48 (TCK)
TDI: JP1.5, U1.45 (TDI)
TDO: JP1.4, U1.83 (TDO)
TMS: JP1.6, U1.47 (TMS)
VCC: IC1.14 (VCC), IC2.3 (VIN), JP2.11, JP8.1, JP8.2, R1.2, R2.2, R3.2, R4.2, R5.2, R6.2, R7.2, R8.2, R9.1, U2.32 (VCC)

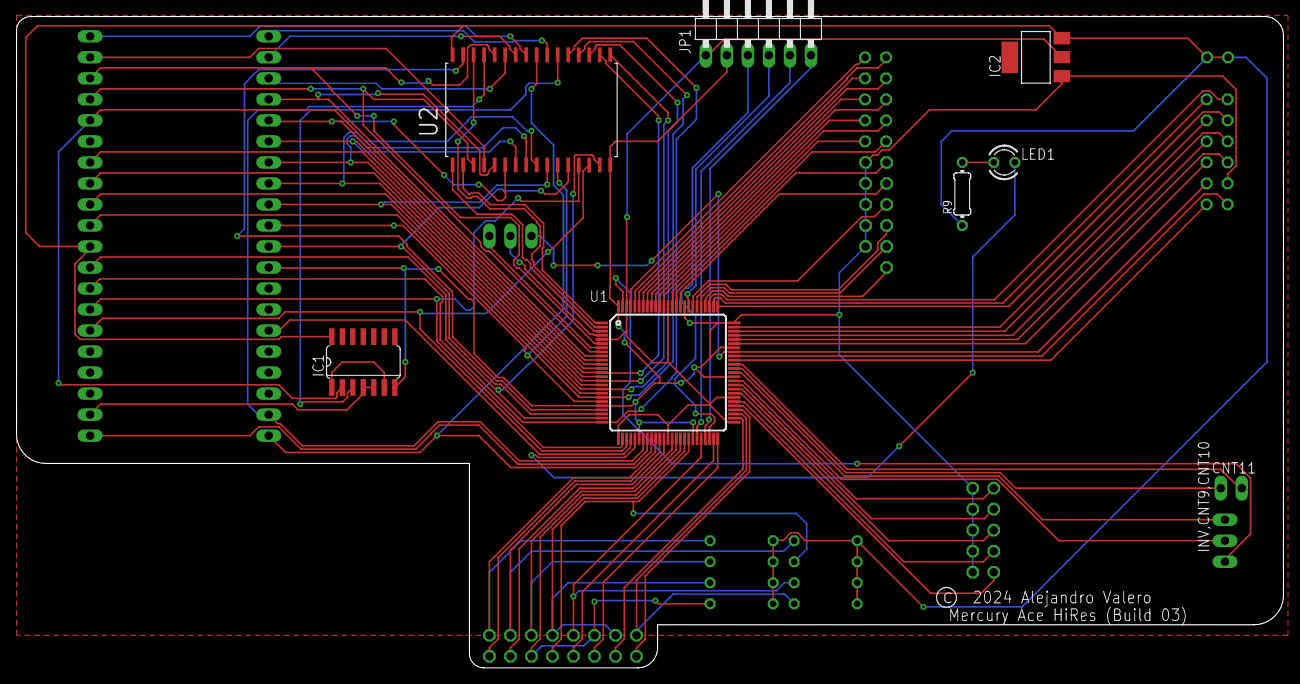
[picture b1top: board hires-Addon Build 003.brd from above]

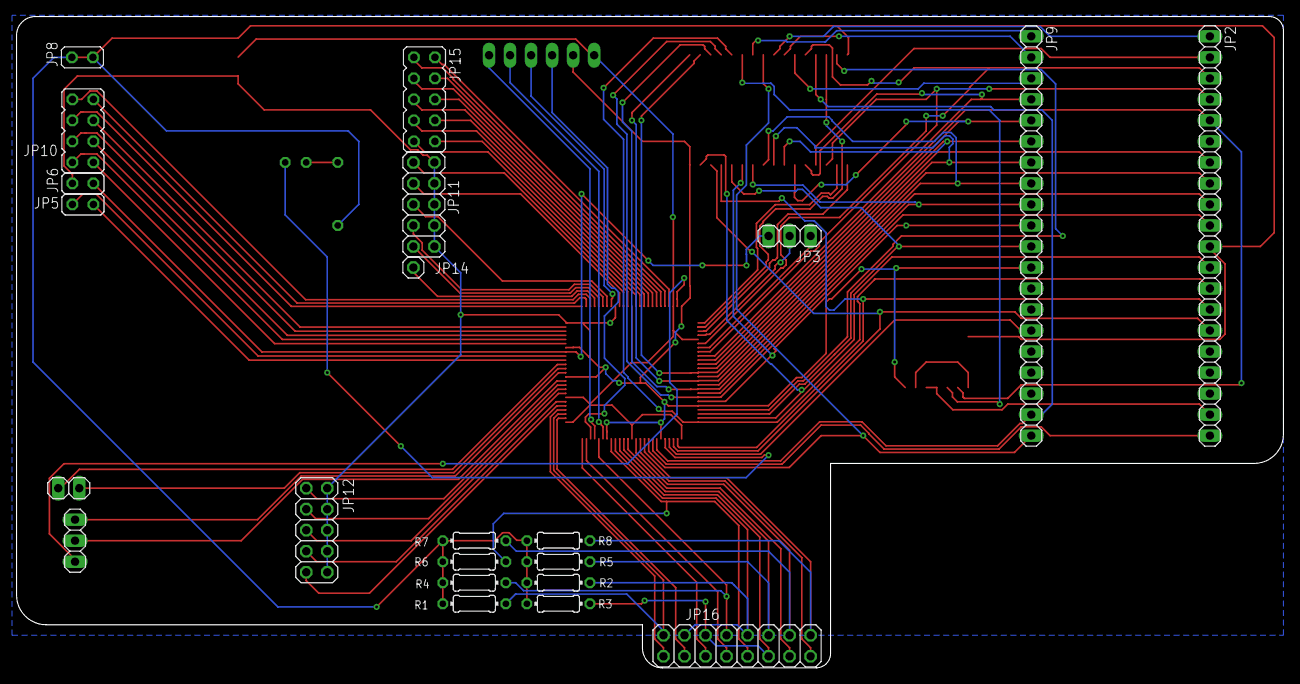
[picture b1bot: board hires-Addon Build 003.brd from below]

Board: 2 copper layers, 153.1 x 78.7 mm, 29 parts (22 on the bottom side), 97 nets.
